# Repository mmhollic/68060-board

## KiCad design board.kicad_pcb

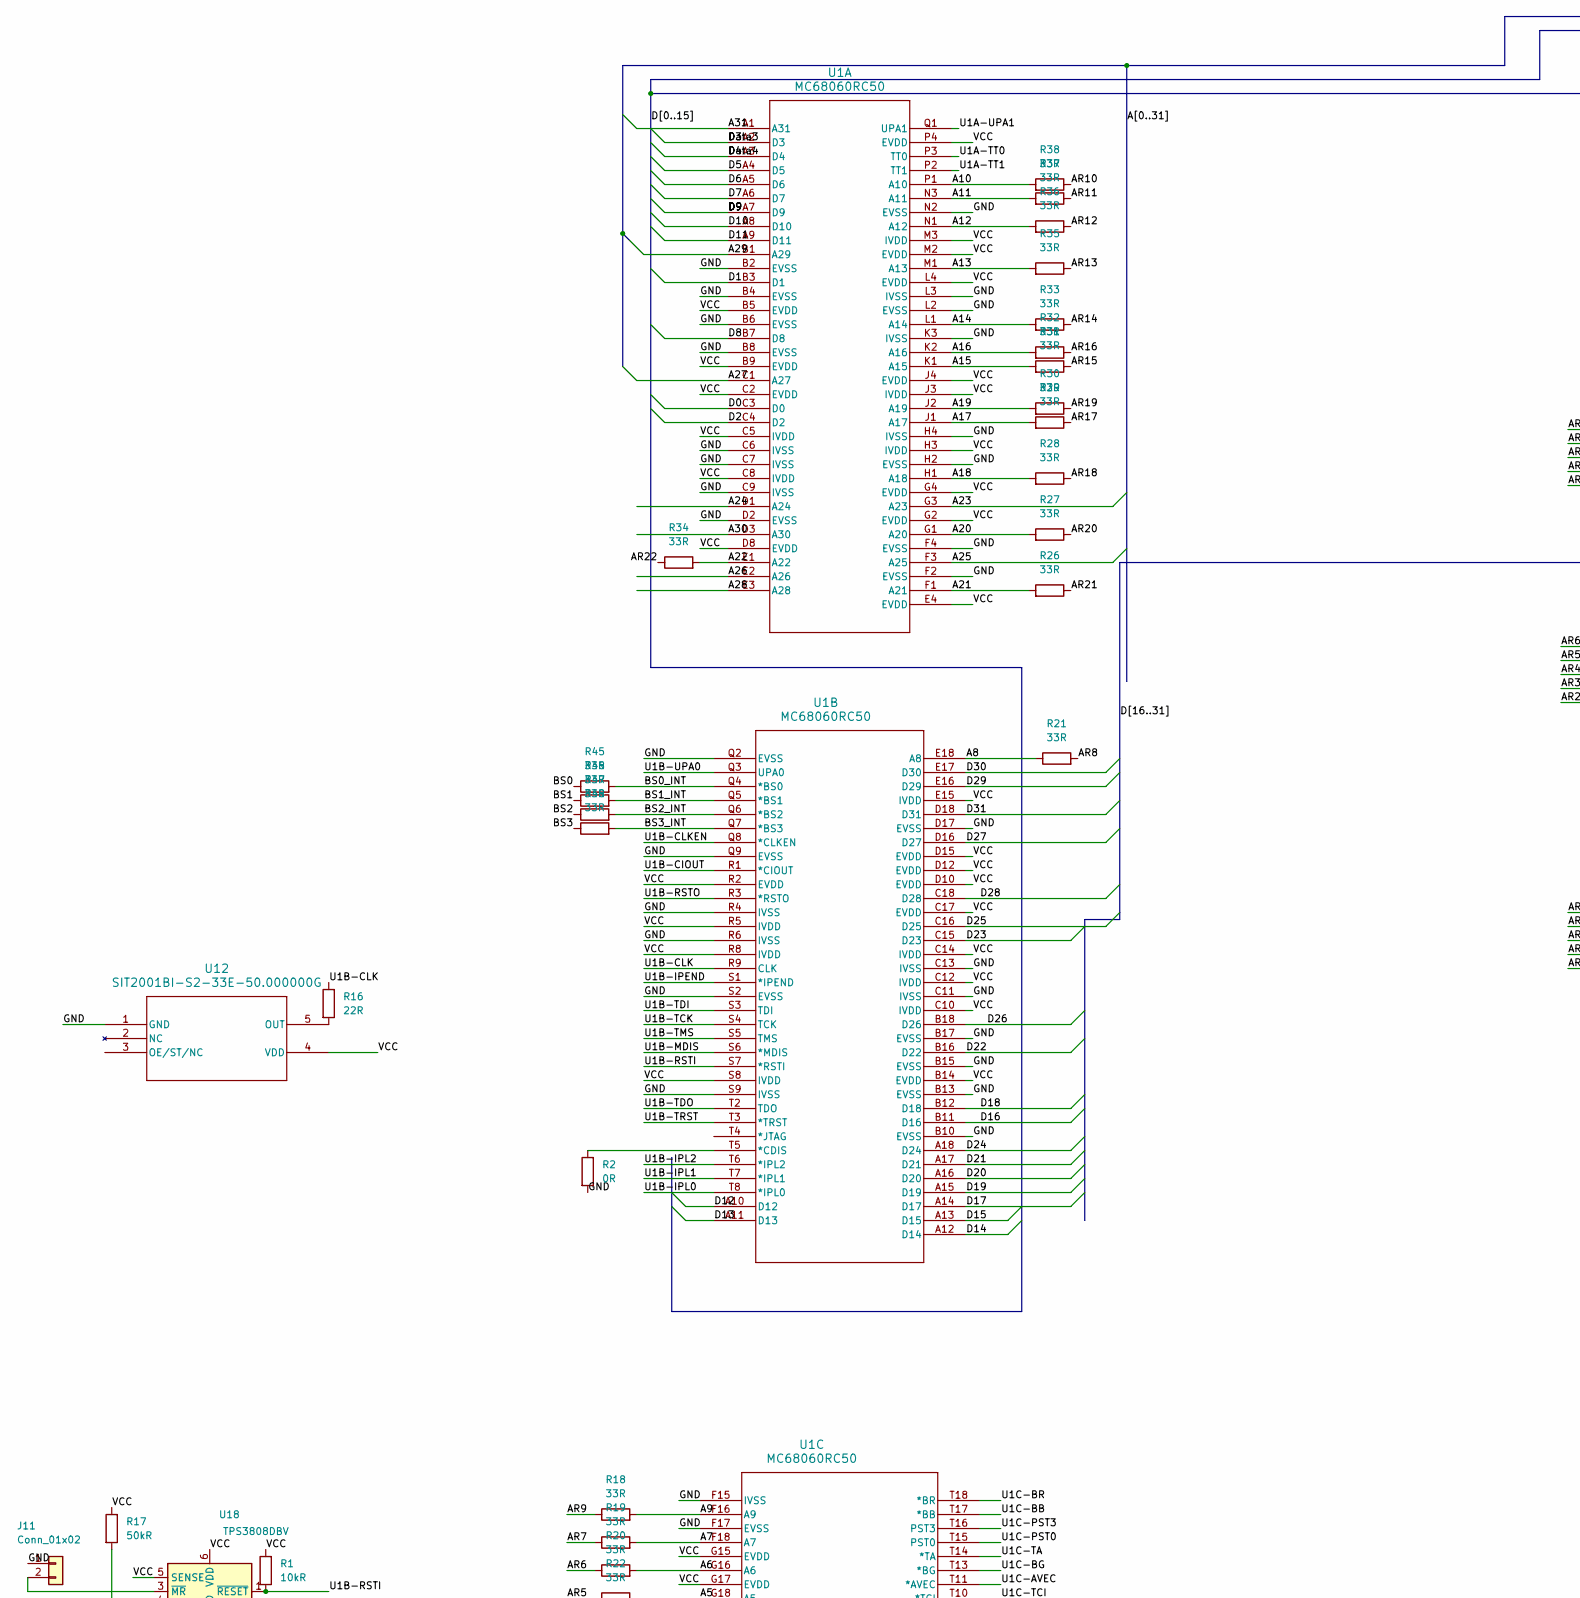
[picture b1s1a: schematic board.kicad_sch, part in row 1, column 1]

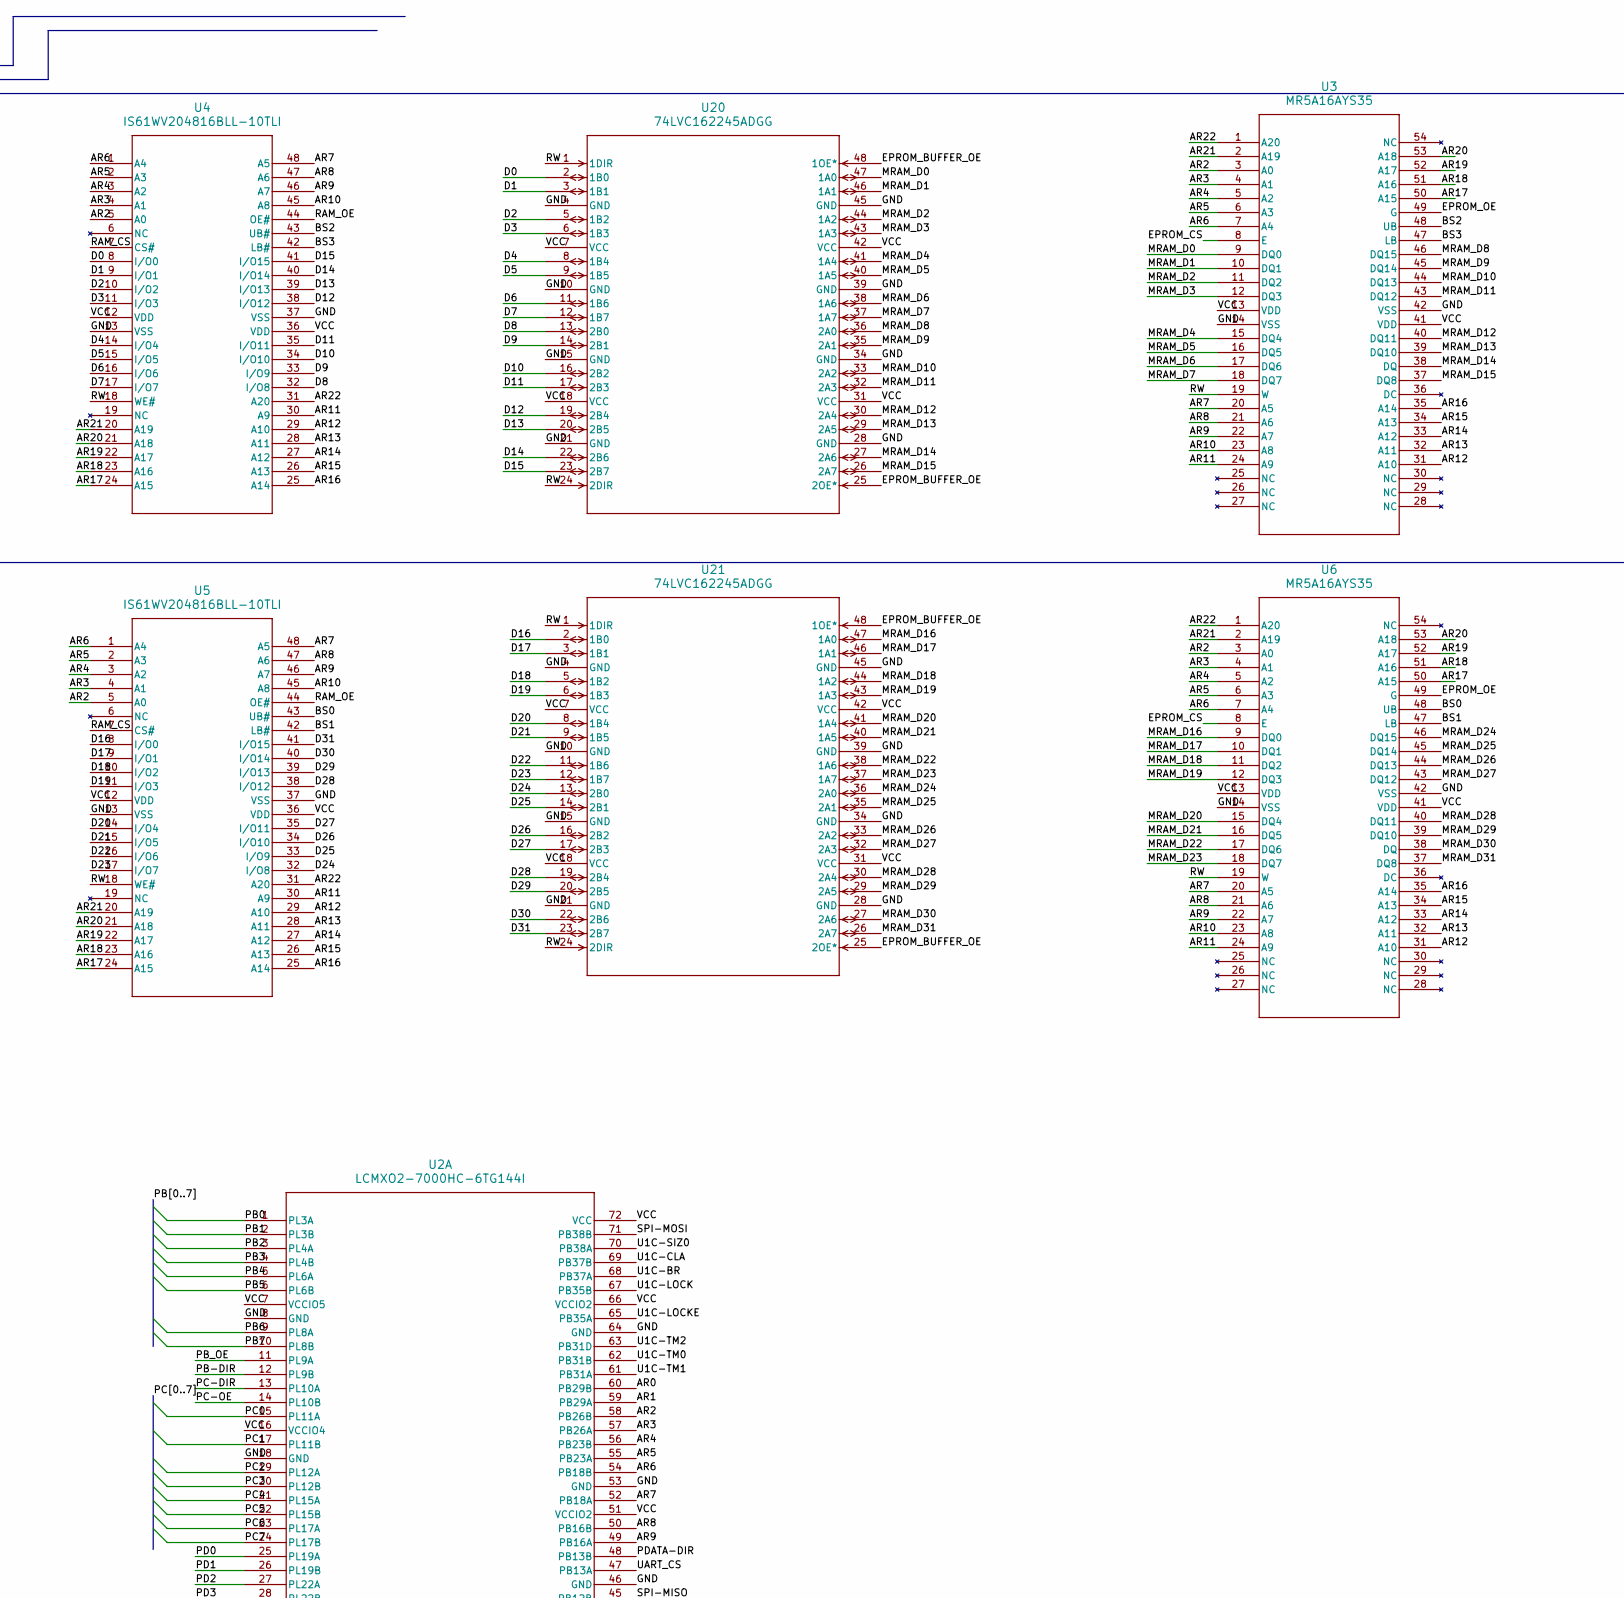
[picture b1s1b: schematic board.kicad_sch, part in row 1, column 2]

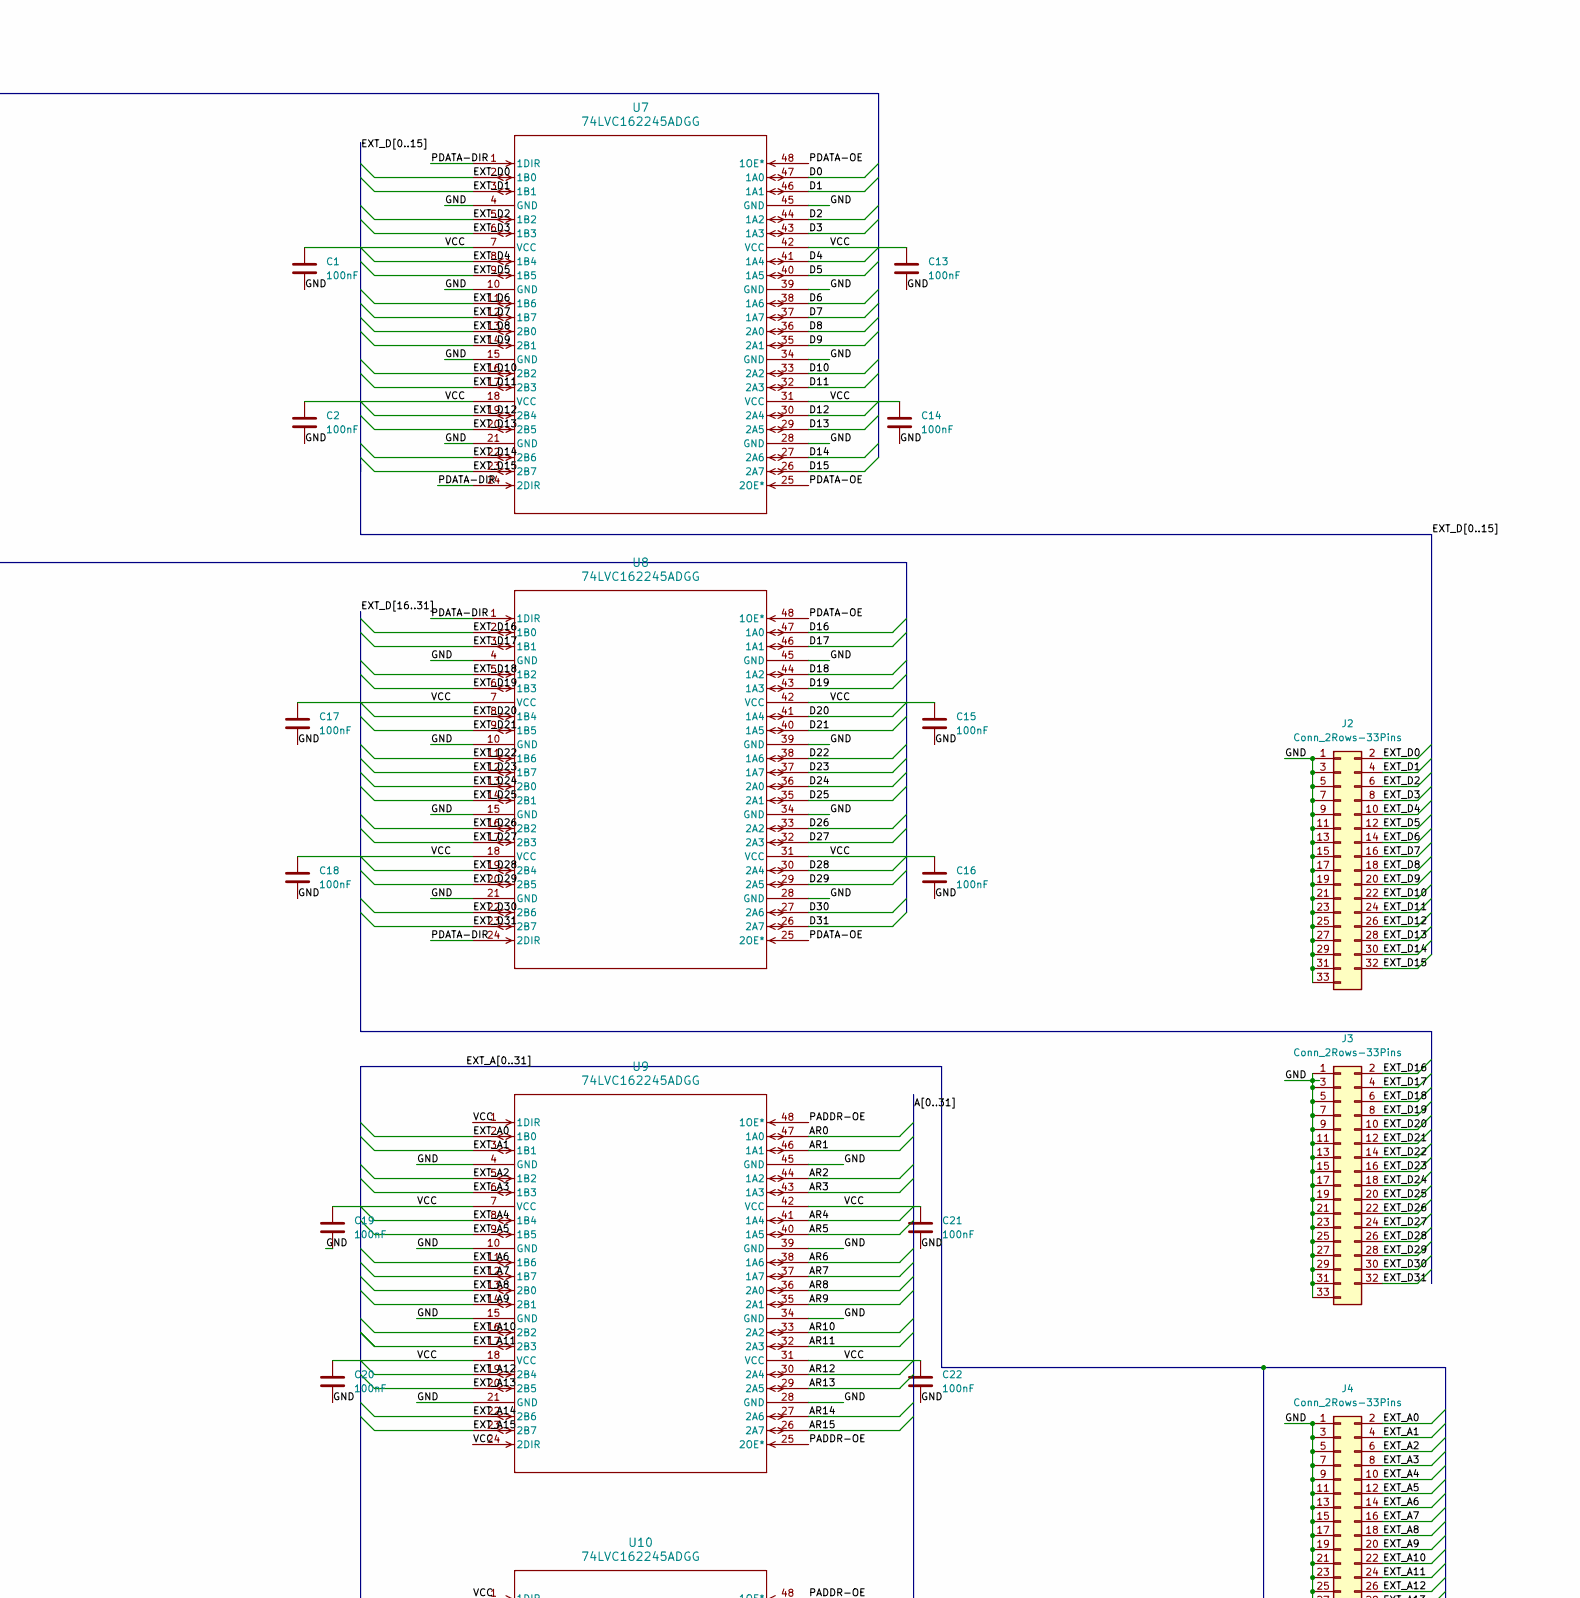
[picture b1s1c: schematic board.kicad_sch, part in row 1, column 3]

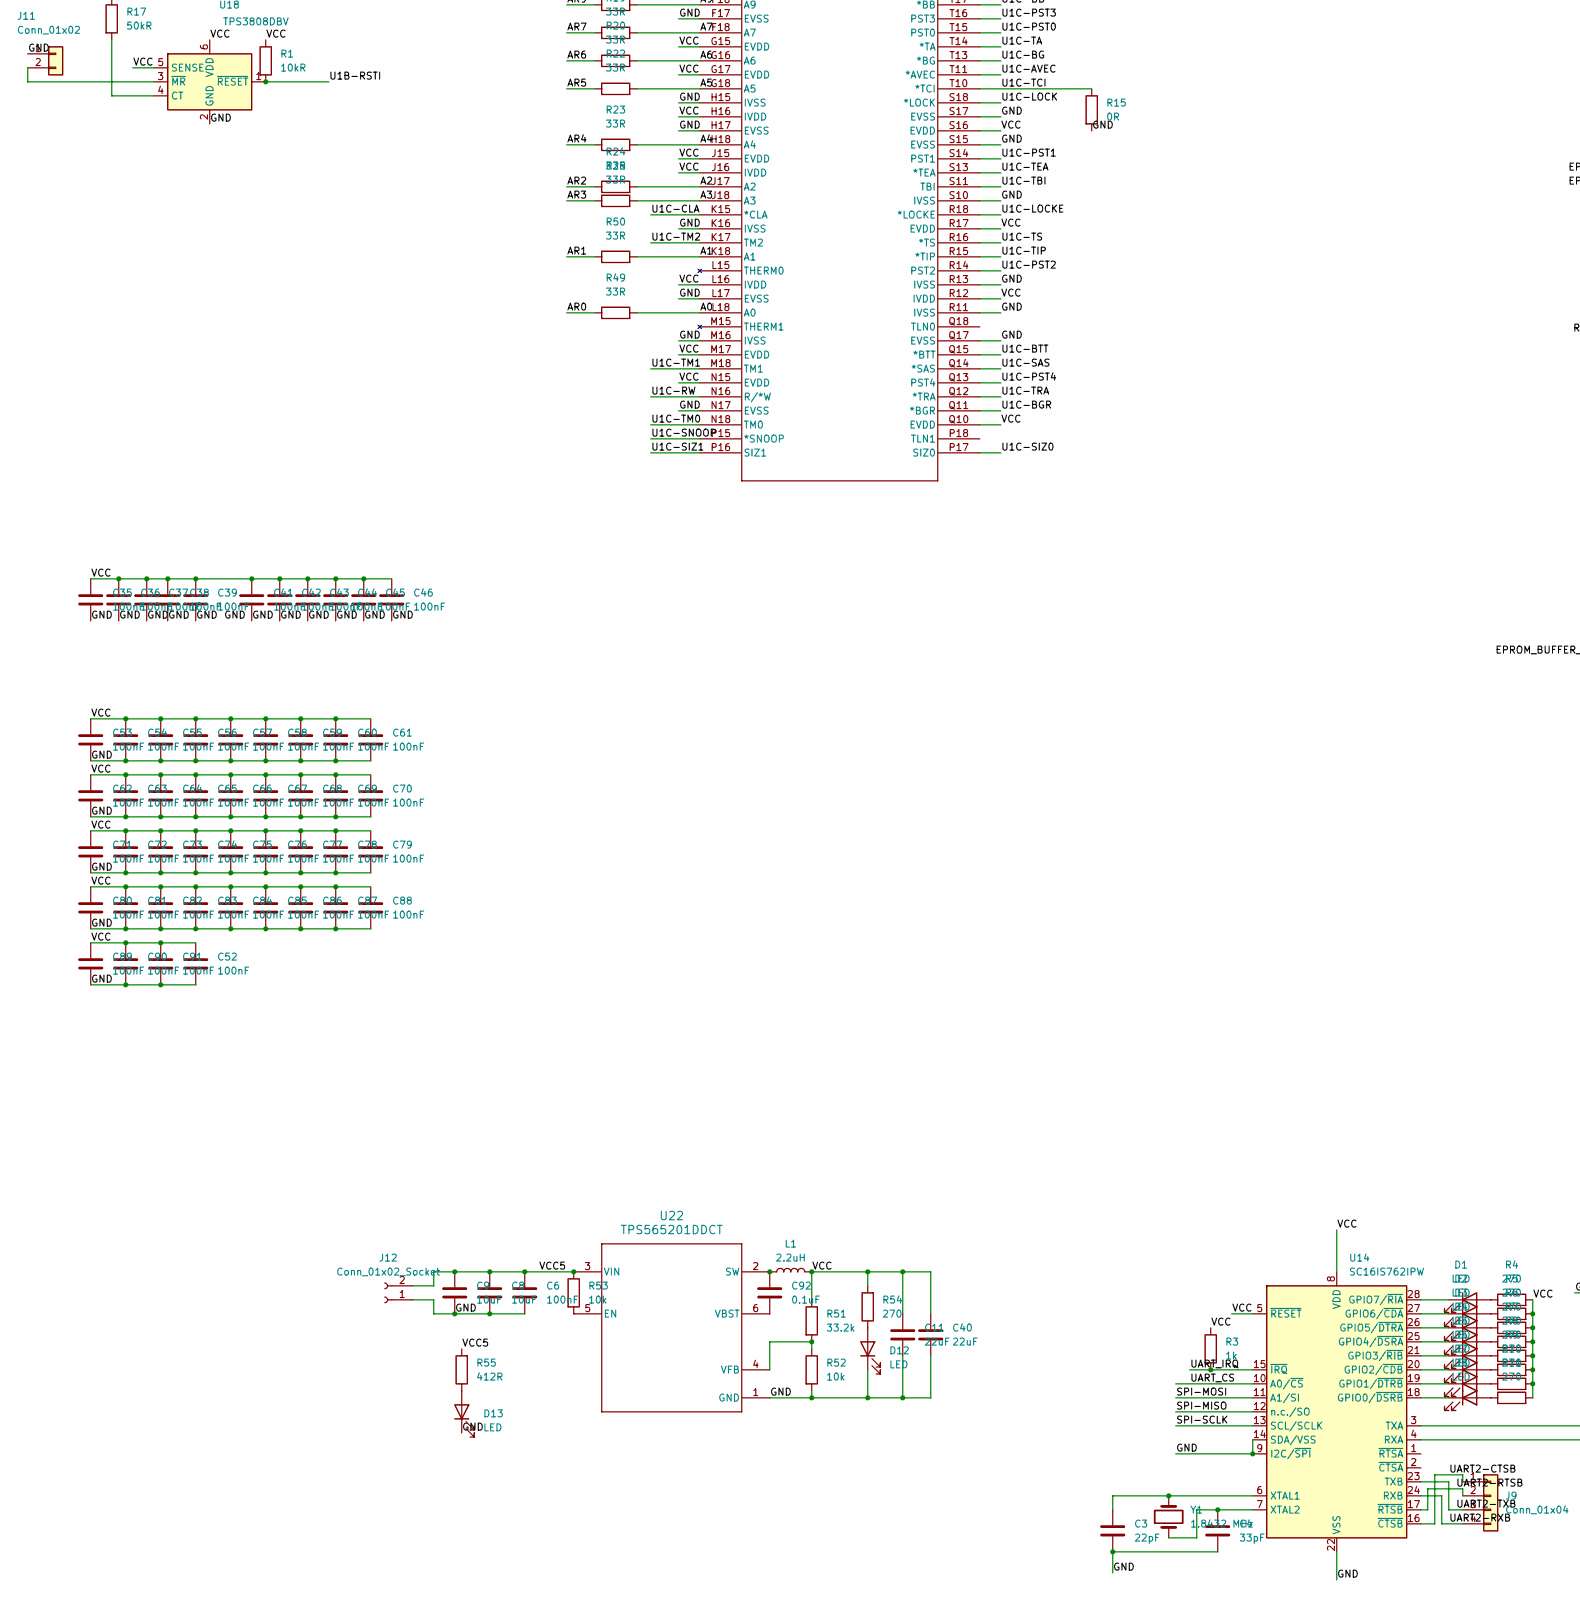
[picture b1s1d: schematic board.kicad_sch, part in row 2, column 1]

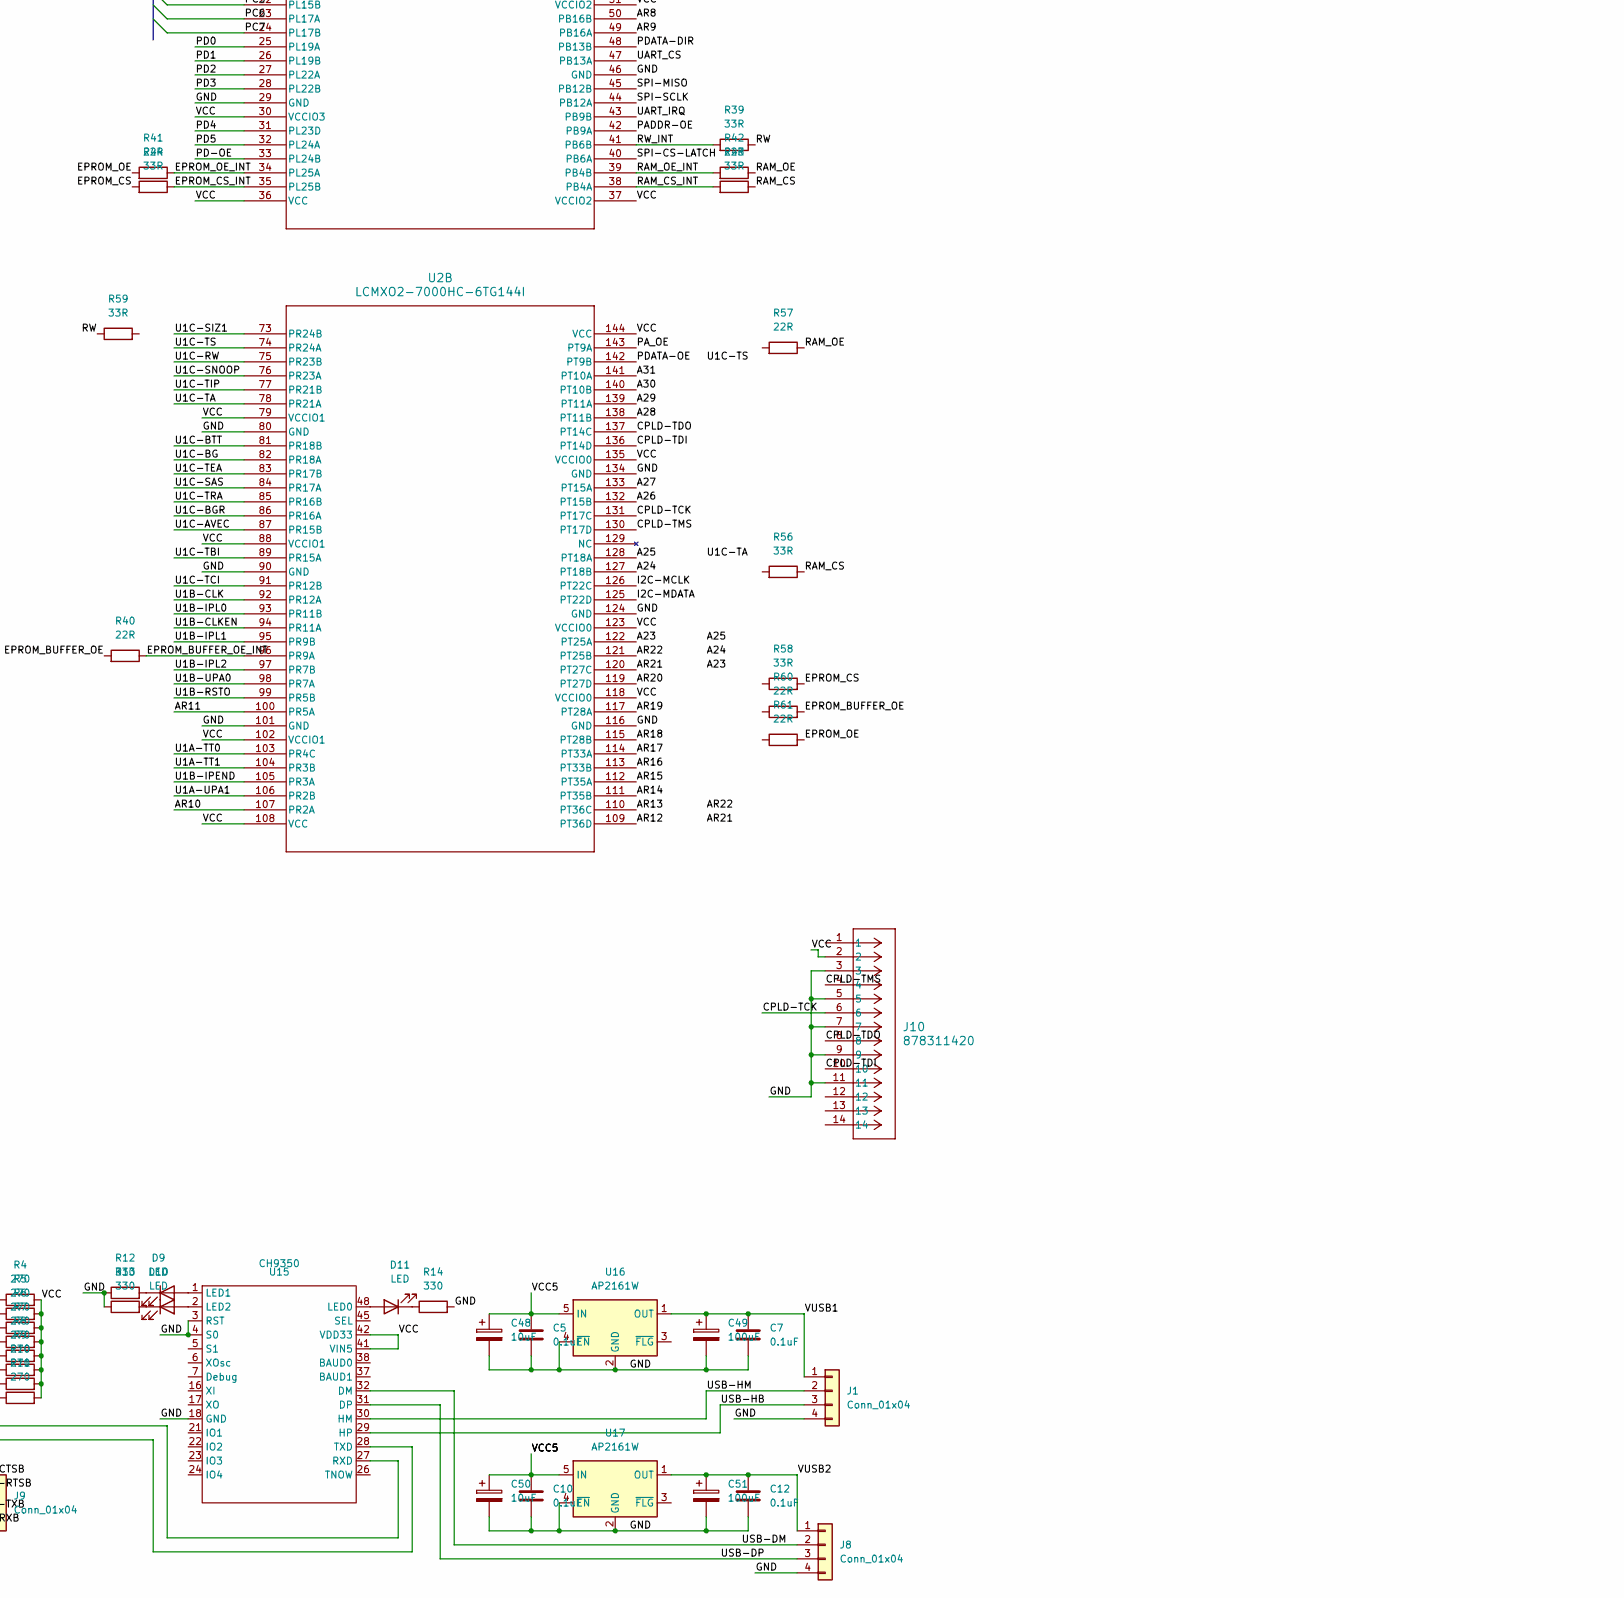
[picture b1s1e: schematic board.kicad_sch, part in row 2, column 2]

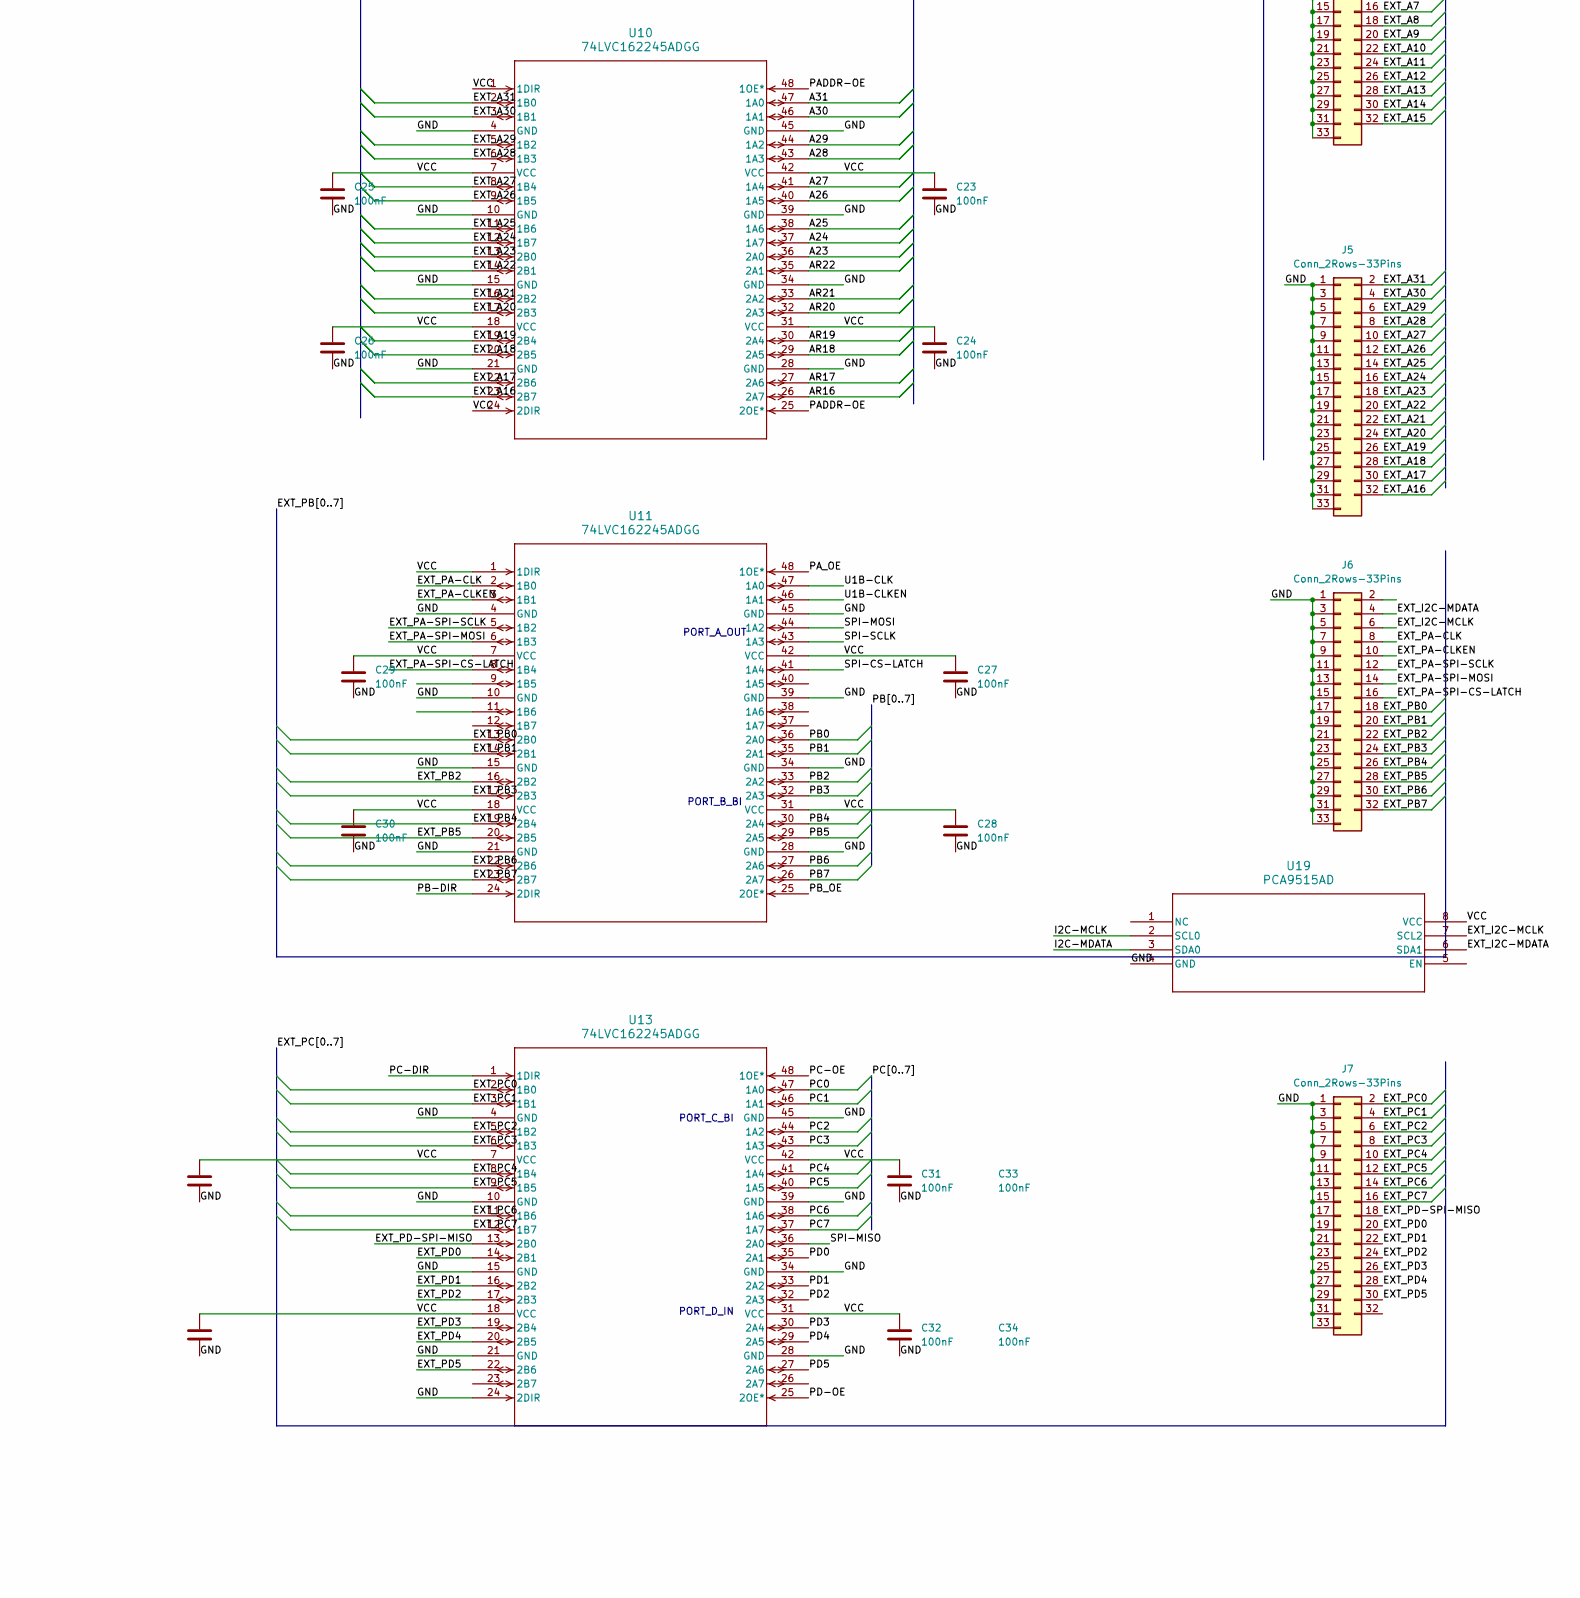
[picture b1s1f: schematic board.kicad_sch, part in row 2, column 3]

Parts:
C1, C2, C6, C13, C14, C15, C16, C17, C18, C19, C20, C21, C22, C23, C24, C25, C26, C27, C28, C29, C30, C31, C32, C33, C34, C35, C36, C37, C38, C39, C41, C42, C43, C44, C45, C46, C52, C53, C54, C55, C56, C57, C58, C59, C60, C61, C62, C63, C64, C65, C66, C67, C68, C69, C70, C71, C72, C73, C74, C75, C76, C77, C78, C79, C80, C81, C82, C83, C84, C85, C86, C87, C88, C89, C90, C91: 100nF; C_0603_1608Metric
C3: 22pF; C_1206_3216Metric_Pad1.33x1.80mm_HandSolder
C4: 33pF; C_1206_3216Metric_Pad1.33x1.80mm_HandSolder
C5, C7, C10, C12: 0.1uF; C_1206_3216Metric_Pad1.33x1.80mm_HandSolder
C8, C9: 10uF; C_1808_4520Metric_Pad1.72x2.30mm_HandSolder
C11, C40: 22uF; C_1206_3216Metric_Pad1.33x1.80mm_HandSolder
C48, C50: 10uF; CP_Elec_4x5.4
C49, C51: 100uF; CP_Elec_6.3x5.4
C92: 0.1uF; C_0603_1608Metric_Pad1.08x0.95mm_HandSolder
D1, D2, D3, D4, D5, D6, D7, D8, D9, D10, D11, D12, D13: LED; LED_1206_3216Metric
J1, J8, J9: Conn_01x04; PinHeader_1x04_P1.00mm_Vertical
J2, J3, J4, J5, J6, J7: Conn_2Rows-33Pins; PinHeader_2x17_P2.54mm_Vertical
J10: 878311420; CONN14_878311420_MOL
J11: Conn_01x02; PinHeader_1x02_P1.00mm_Vertical
J12: Conn_01x02_Socket; CONN_SD-5566-002_02_MOL
L1: 2.2uH; IND_1111-WE-TIS_WRE
R1: 10kR; R_0805_2012Metric_Pad1.20x1.40mm_HandSolder
R2, R15: 0R; R_0805_2012Metric_Pad1.20x1.40mm_HandSolder
R3: 1k; R_0805_2012Metric_Pad1.20x1.40mm_HandSolder
R4, R5, R6, R7, R8, R9, R10, R11, R54: 270; R_0805_2012Metric_Pad1.20x1.40mm_HandSolder
R12, R13, R14: 330; R_0805_2012Metric_Pad1.20x1.40mm_HandSolder
R16: 22R; R_0805_2012Metric_Pad1.20x1.40mm_HandSolder
R17: 50kR; R_0805_2012Metric_Pad1.20x1.40mm_HandSolder
R18, R19, R20, R21, R22, R23, R24, R25, R26, R27, R28, R29, R30, R31, R32, R33, R34, R35, R36, R37, R38, R39, R43, R44, R45, R46, R47, R48, R49, R50, R56, R58, R59: 33R; R_0201_0603Metric_Pad0.64x0.40mm_HandSolder
R40, R41, R42, R57, R60, R61: 22R; R_0201_0603Metric_Pad0.64x0.40mm_HandSolder
R51: 33.2k; R_Axial_DIN0204_L3.6mm_D1.6mm_P5.08mm_Horizontal
R52, R53: 10k; R_Axial_DIN0204_L3.6mm_D1.6mm_P5.08mm_Horizontal
R55: 412R; R_0603_1608Metric
U1: MC68060RC50; PGA206_SOT555-4_NXP
U2: LCMXO2-7000HC-6TG144I; TQFP144_LAT
U3, U6: MR5A16AYS35; TSOP54_MR5A16_10P16X22P22_EVS
U4, U5: IS61WV204816BLL-10TLI; 48L_TSOP-1_12X20_ISI
U7, U8, U9, U10, U11, U13, U20, U21: 74LVC162245ADGG; SOT362-1_NEX
U12: SIT2001BI-S2-33E-50.000000G; SOT_SiT1630-S_SIT
U14: SC16IS762IPW; TSSOP-28_4.4x9.7mm_P0.65mm
U15: CH9350; LQFP-48_7x7mm_P0.5mm
U16, U17: AP2161W; SOT-23-5
U18: TPS3808DBV; SOT-23-6
U19: PCA9515AD; SOT96-1_NXP
U22: TPS565201DDCT; DDC0006A_N
Y1: 1.8432 MHz; Crystal_HC49-U_Vertical

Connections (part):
/A0: R49.2, U1.L18 (A0)
/A1: R50.2, U1.K18 (A1)
/A2: R24.2, U1.J17 (A2)
/A3: R25.2, U1.J18 (A3)
/A4: R23.2, U1.H18 (A4)
/A5: R22.2, U1.G18 (A5)
/A6: R20.2, U1.G16 (A6)
/A7: R19.2, U1.F18 (A7)
/A8: R21.1, U1.E18 (A8)
/A9: R18.2, U1.F16 (A9)
/A10: R38.2, U1.P1 (A10)
/A11: R37.2, U1.N3 (A11)
/A12: R36.2, U1.N1 (A12)
/A13: R35.2, U1.M1 (A13)
/A14: R33.2, U1.L1 (A14)
/A15: R31.2, U1.K1 (A15)
/A16: R32.2, U1.K2 (A16)
/A17: R29.2, U1.J1 (A17)
/A18: R28.2, U1.H1 (A18)
/A19: R30.2, U1.J2 (A19)
/A20: R27.2, U1.G1 (A20)
/A21: R26.2, U1.F1 (A21)
/A22: R34.2, U1.E1 (A22)
/A23: U1.G3 (A23), U2.122 (PT25A), U10.36 (2A0)
/A24: U1.D1 (A24), U2.127 (PT18B), U10.37 (1A7)
/A25: U1.F3 (A25), U2.128 (PT18A), U10.38 (1A6)
/A26: U1.E2 (A26), U2.132 (PT15B), U10.40 (1A5)
/A27: U1.C1 (A27), U2.133 (PT15A), U10.41 (1A4)
/A28: U1.E3 (A28), U2.138 (PT11B), U10.43 (1A3)
/A29: U1.B1 (A29), U2.139 (PT11A), U10.44 (1A2)
/A30: U1.D3 (A30), U2.140 (PT10B), U10.46 (1A1)
/A31: U1.A1 (A31), U2.141 (PT10A), U10.47 (1A0)
/AR0: R49.1, U2.60 (PB29B), U9.47 (1A0)
/AR1: R50.1, U2.59 (PB29A), U9.46 (1A1)
/AR2: R24.1, U2.58 (PB26B), U3.3 (A0), U4.5 (A0), U5.5 (A0), U6.3 (A0), U9.44 (1A2)
/AR3: R25.1, U2.57 (PB26A), U3.4 (A1), U4.4 (A1), U5.4 (A1), U6.4 (A1), U9.43 (1A3)
/AR4: R23.1, U2.56 (PB23B), U3.5 (A2), U4.3 (A2), U5.3 (A2), U6.5 (A2), U9.41 (1A4)
/AR5: R22.1, U2.55 (PB23A), U3.6 (A3), U4.2 (A3), U5.2 (A3), U6.6 (A3), U9.40 (1A5)
/AR6: R20.1, U2.54 (PB18B), U3.7 (A4), U4.1 (A4), U5.1 (A4), U6.7 (A4), U9.38 (1A6)
/AR7: R19.1, U2.52 (PB18A), U3.20 (A5), U4.48 (A5), U5.48 (A5), U6.20 (A5), U9.37 (1A7)
/AR8: R21.2, U2.50 (PB16B), U3.21 (A6), U4.47 (A6), U5.47 (A6), U6.21 (A6), U9.36 (2A0)
/AR9: R18.1, U2.49 (PB16A), U3.22 (A7), U4.46 (A7), U5.46 (A7), U6.22 (A7), U9.35 (2A1)
/AR10: R38.1, U2.107 (PR2A), U3.23 (A8), U4.45 (A8), U5.45 (A8), U6.23 (A8), U9.33 (2A2)
/AR11: R37.1, U2.100 (PR5A), U3.24 (A9), U4.30 (A9), U5.30 (A9), U6.24 (A9), U9.32 (2A3)
/AR12: R36.1, U2.109 (PT36D), U3.31 (A10), U4.29 (A10), U5.29 (A10), U6.31 (A10), U9.30 (2A4)
/AR13: R35.1, U2.110 (PT36C), U3.32 (A11), U4.28 (A11), U5.28 (A11), U6.32 (A11), U9.29 (2A5)
/AR14: R33.1, U2.111 (PT35B), U3.33 (A12), U4.27 (A12), U5.27 (A12), U6.33 (A12), U9.27 (2A6)
/AR15: R31.1, U2.112 (PT35A), U3.34 (A13), U4.26 (A13), U5.26 (A13), U6.34 (A13), U9.26 (2A7)
/AR16: R32.1, U2.113 (PT33B), U3.35 (A14), U4.25 (A14), U5.25 (A14), U6.35 (A14), U10.26 (2A7)
/AR17: R29.1, U2.114 (PT33A), U3.50 (A15), U4.24 (A15), U5.24 (A15), U6.50 (A15), U10.27 (2A6)
/AR18: R28.1, U2.115 (PT28B), U3.51 (A16), U4.23 (A16), U5.23 (A16), U6.51 (A16), U10.29 (2A5)
/AR19: R30.1, U2.117 (PT28A), U3.52 (A17), U4.22 (A17), U5.22 (A17), U6.52 (A17), U10.30 (2A4)
/AR20: R27.1, U2.119 (PT27D), U3.53 (A18), U4.21 (A18), U5.21 (A18), U6.53 (A18), U10.32 (2A3)
/AR21: R26.1, U2.120 (PT27C), U3.2 (A19), U4.20 (A19), U5.20 (A19), U6.2 (A19), U10.33 (2A2)
/AR22: R34.1, U2.121 (PT25B), U3.1 (A20), U4.31 (A20), U5.31 (A20), U6.1 (A20), U10.35 (2A1)
/BS0: R45.1, U5.43 (UB#), U6.48 (UB)
/BS0_INT: R45.2, U1.Q4 (*BS0)
/BS1: R46.1, U5.42 (LB#), U6.47 (LB)
/BS1_INT: R46.2, U1.Q5 (*BS1)
/BS2: R47.1, U3.48 (UB), U4.43 (UB#)
/BS2_INT: R47.2, U1.Q6 (*BS2)
/BS3: R48.1, U3.47 (LB), U4.42 (LB#)
/BS3_INT: R48.2, U1.Q7 (*BS3)
/CPLD-TCK: J10.6, U2.131 (PT17C)
/CPLD-TDI: J10.10, U2.136 (PT14D)
/CPLD-TDO: J10.8, U2.137 (PT14C)
/CPLD-TMS: J10.4, U2.130 (PT17D)
/D0: U1.C3 (D0), U4.8 (I/O0), U7.47 (1A0), U20.2 (1B0)
/D1: U1.B3 (D1), U4.9 (I/O1), U7.46 (1A1), U20.3 (1B1)
/D2: U1.C4 (D2), U4.10 (I/O2), U7.44 (1A2), U20.5 (1B2)
/D3: U1.A2 (D3), U4.11 (I/O3), U7.43 (1A3), U20.6 (1B3)
/D4: U1.A3 (D4), U4.14 (I/O4), U7.41 (1A4), U20.8 (1B4)
/D5: U1.A4 (D5), U4.15 (I/O5), U7.40 (1A5), U20.9 (1B5)
/D6: U1.A5 (D6), U4.16 (I/O6), U7.38 (1A6), U20.11 (1B6)
/D7: U1.A6 (D7), U4.17 (I/O7), U7.37 (1A7), U20.12 (1B7)
/D8: U1.B7 (D8), U4.32 (I/O8), U7.36 (2A0), U20.13 (2B0)
/D9: U1.A7 (D9), U4.33 (I/O9), U7.35 (2A1), U20.14 (2B1)
/D10: U1.A8 (D10), U4.34 (I/O10), U7.33 (2A2), U20.16 (2B2)
/D11: U1.A9 (D11), U4.35 (I/O11), U7.32 (2A3), U20.17 (2B3)
/D12: U1.A10 (D12), U4.38 (I/O12), U7.30 (2A4), U20.19 (2B4)
/D13: U1.A11 (D13), U4.39 (I/O13), U7.29 (2A5), U20.20 (2B5)
/D14: U1.A12 (D14), U4.40 (I/O14), U7.27 (2A6), U20.22 (2B6)
/D15: U1.A13 (D15), U4.41 (I/O15), U7.26 (2A7), U20.23 (2B7)
/D16: U1.B11 (D16), U5.8 (I/O0), U8.47 (1A0), U21.2 (1B0)
/D17: U1.A14 (D17), U5.9 (I/O1), U8.46 (1A1), U21.3 (1B1)
/D18: U1.B12 (D18), U5.10 (I/O2), U8.44 (1A2), U21.5 (1B2)
/D19: U1.A15 (D19), U5.11 (I/O3), U8.43 (1A3), U21.6 (1B3)
/D20: U1.A16 (D20), U5.14 (I/O4), U8.41 (1A4), U21.8 (1B4)
/D21: U1.A17 (D21), U5.15 (I/O5), U8.40 (1A5), U21.9 (1B5)
/D22: U1.B16 (D22), U5.16 (I/O6), U8.38 (1A6), U21.11 (1B6)
/D23: U1.C15 (D23), U5.17 (I/O7), U8.37 (1A7), U21.12 (1B7)
/D24: U1.A18 (D24), U5.32 (I/O8), U8.36 (2A0), U21.13 (2B0)
/D25: U1.C16 (D25), U5.33 (I/O9), U8.35 (2A1), U21.14 (2B1)
/D26: U1.B18 (D26), U5.34 (I/O10), U8.33 (2A2), U21.16 (2B2)
/D27: U1.D16 (D27), U5.35 (I/O11), U8.32 (2A3), U21.17 (2B3)
/D28: U1.C18 (D28), U5.38 (I/O12), U8.30 (2A4), U21.19 (2B4)
/D29: U1.E16 (D29), U5.39 (I/O13), U8.29 (2A5), U21.20 (2B5)
/D30: U1.E17 (D30), U5.40 (I/O14), U8.27 (2A6), U21.22 (2B6)
/D31: U1.D18 (D31), U5.41 (I/O15), U8.26 (2A7), U21.23 (2B7)
/EPROM_BUFFER_OE: R40.2, R60.2, U20.25 (2OE*), U20.48 (1OE*), U21.25 (2OE*), U21.48 (1OE*)
/EPROM_BUFFER_OE_INT: R40.1, U2.96 (PR9A)
/EPROM_CS: R44.2, R58.2, U3.8 (E), U6.8 (E)
/EPROM_CS_INT: R44.1, U2.35 (PL25B)
/EPROM_OE: R41.2, R61.2, U3.49 (G), U6.49 (G)
/EPROM_OE_INT: R41.1, U2.34 (PL25A)
/EXT_A0: J4.2, U9.2 (1B0)
/EXT_A1: J4.4, U9.3 (1B1)
/EXT_A2: J4.6, U9.5 (1B2)
/EXT_A3: J4.8, U9.6 (1B3)
/EXT_A4: J4.10, U9.8 (1B4)
/EXT_A5: J4.12, U9.9 (1B5)
/EXT_A6: J4.14, U9.11 (1B6)
/EXT_A7: J4.16, U9.12 (1B7)
/EXT_A8: J4.18, U9.13 (2B0)
/EXT_A9: J4.20, U9.14 (2B1)
/EXT_A10: J4.22, U9.16 (2B2)
/EXT_A11: J4.24, U9.17 (2B3)
/EXT_A12: J4.26, U9.19 (2B4)
/EXT_A13: J4.28, U9.20 (2B5)
/EXT_A14: J4.30, U9.22 (2B6)
/EXT_A15: J4.32, U9.23 (2B7)
/EXT_A16: J5.32, U10.23 (2B7)
/EXT_A17: J5.30, U10.22 (2B6)
/EXT_A18: J5.28, U10.20 (2B5)
/EXT_A19: J5.26, U10.19 (2B4)
/EXT_A20: J5.24, U10.17 (2B3)
/EXT_A21: J5.22, U10.16 (2B2)
/EXT_A22: J5.20, U10.14 (2B1)
/EXT_A23: J5.18, U10.13 (2B0)
/EXT_A24: J5.16, U10.12 (1B7)
/EXT_A25: J5.14, U10.11 (1B6)
/EXT_A26: J5.12, U10.9 (1B5)
/EXT_A27: J5.10, U10.8 (1B4)
/EXT_A28: J5.8, U10.6 (1B3)
/EXT_A29: J5.6, U10.5 (1B2)
/EXT_A30: J5.4, U10.3 (1B1)
/EXT_A31: J5.2, U10.2 (1B0)
/EXT_D0: J2.2, U7.2 (1B0)
/EXT_D1: J2.4, U7.3 (1B1)
/EXT_D2: J2.6, U7.5 (1B2)
/EXT_D3: J2.8, U7.6 (1B3)
/EXT_D4: J2.10, U7.8 (1B4)
/EXT_D5: J2.12, U7.9 (1B5)
/EXT_D6: J2.14, U7.11 (1B6)
/EXT_D7: J2.16, U7.12 (1B7)
/EXT_D8: J2.18, U7.13 (2B0)
/EXT_D9: J2.20, U7.14 (2B1)
/EXT_D10: J2.22, U7.16 (2B2)
/EXT_D11: J2.24, U7.17 (2B3)
/EXT_D12: J2.26, U7.19 (2B4)
/EXT_D13: J2.28, U7.20 (2B5)
/EXT_D14: J2.30, U7.22 (2B6)
/EXT_D15: J2.32, U7.23 (2B7)
/EXT_D16: J3.2, U8.2 (1B0)
/EXT_D17: J3.4, U8.3 (1B1)
/EXT_D18: J3.6, U8.5 (1B2)
/EXT_D19: J3.8, U8.6 (1B3)
/EXT_D20: J3.10, U8.8 (1B4)
/EXT_D21: J3.12, U8.9 (1B5)
/EXT_D22: J3.14, U8.11 (1B6)
/EXT_D23: J3.16, U8.12 (1B7)
/EXT_D24: J3.18, U8.13 (2B0)
/EXT_D25: J3.20, U8.14 (2B1)
/EXT_D26: J3.22, U8.16 (2B2)
/EXT_D27: J3.24, U8.17 (2B3)
/EXT_D28: J3.26, U8.19 (2B4)
/EXT_D29: J3.28, U8.20 (2B5)
/EXT_D30: J3.30, U8.22 (2B6)
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
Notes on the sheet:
PORT_D_IN
PORT_B_BI
PORT_C_BI
PORT_A_OUT

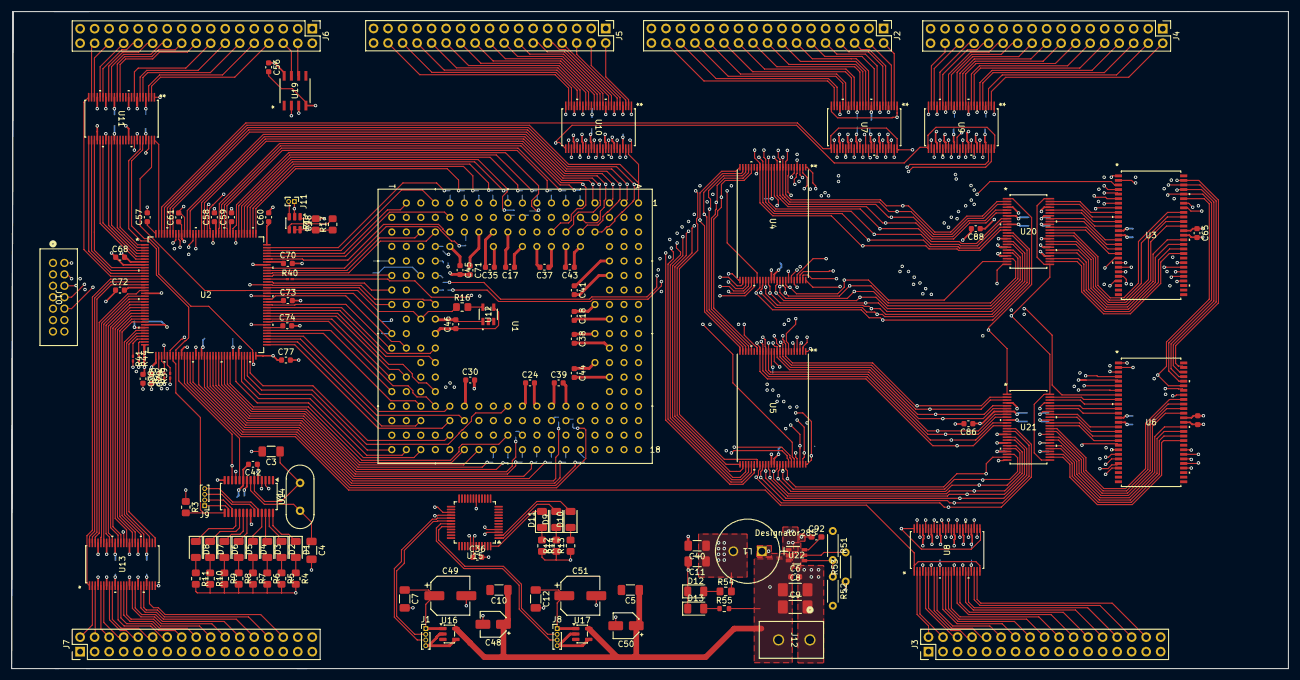
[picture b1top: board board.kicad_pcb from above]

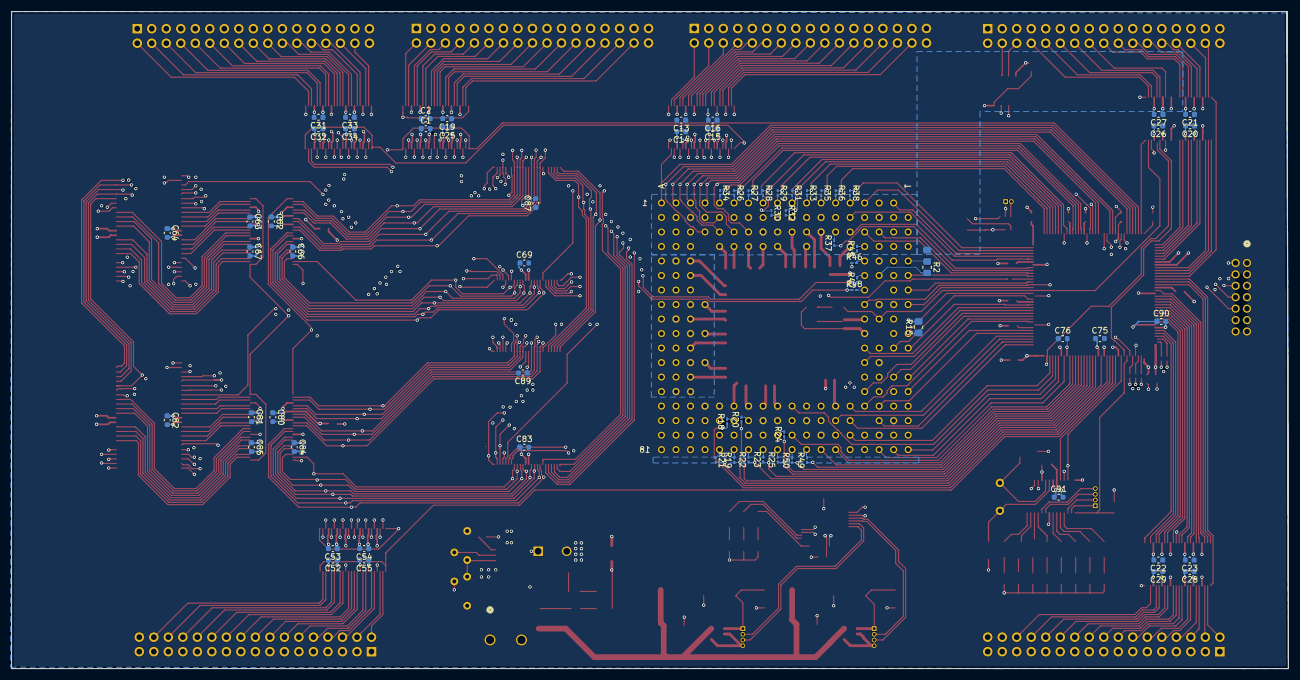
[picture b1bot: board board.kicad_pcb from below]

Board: 6 copper layers, 223.5 x 115.0 mm, 195 parts (71 on the bottom side), 360 nets.
